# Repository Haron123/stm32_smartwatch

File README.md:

# stm32_smartwatch
a Project in which i Design a PCB for a STM32 based Smartwatch and eventually Programm it with FreeRTOS

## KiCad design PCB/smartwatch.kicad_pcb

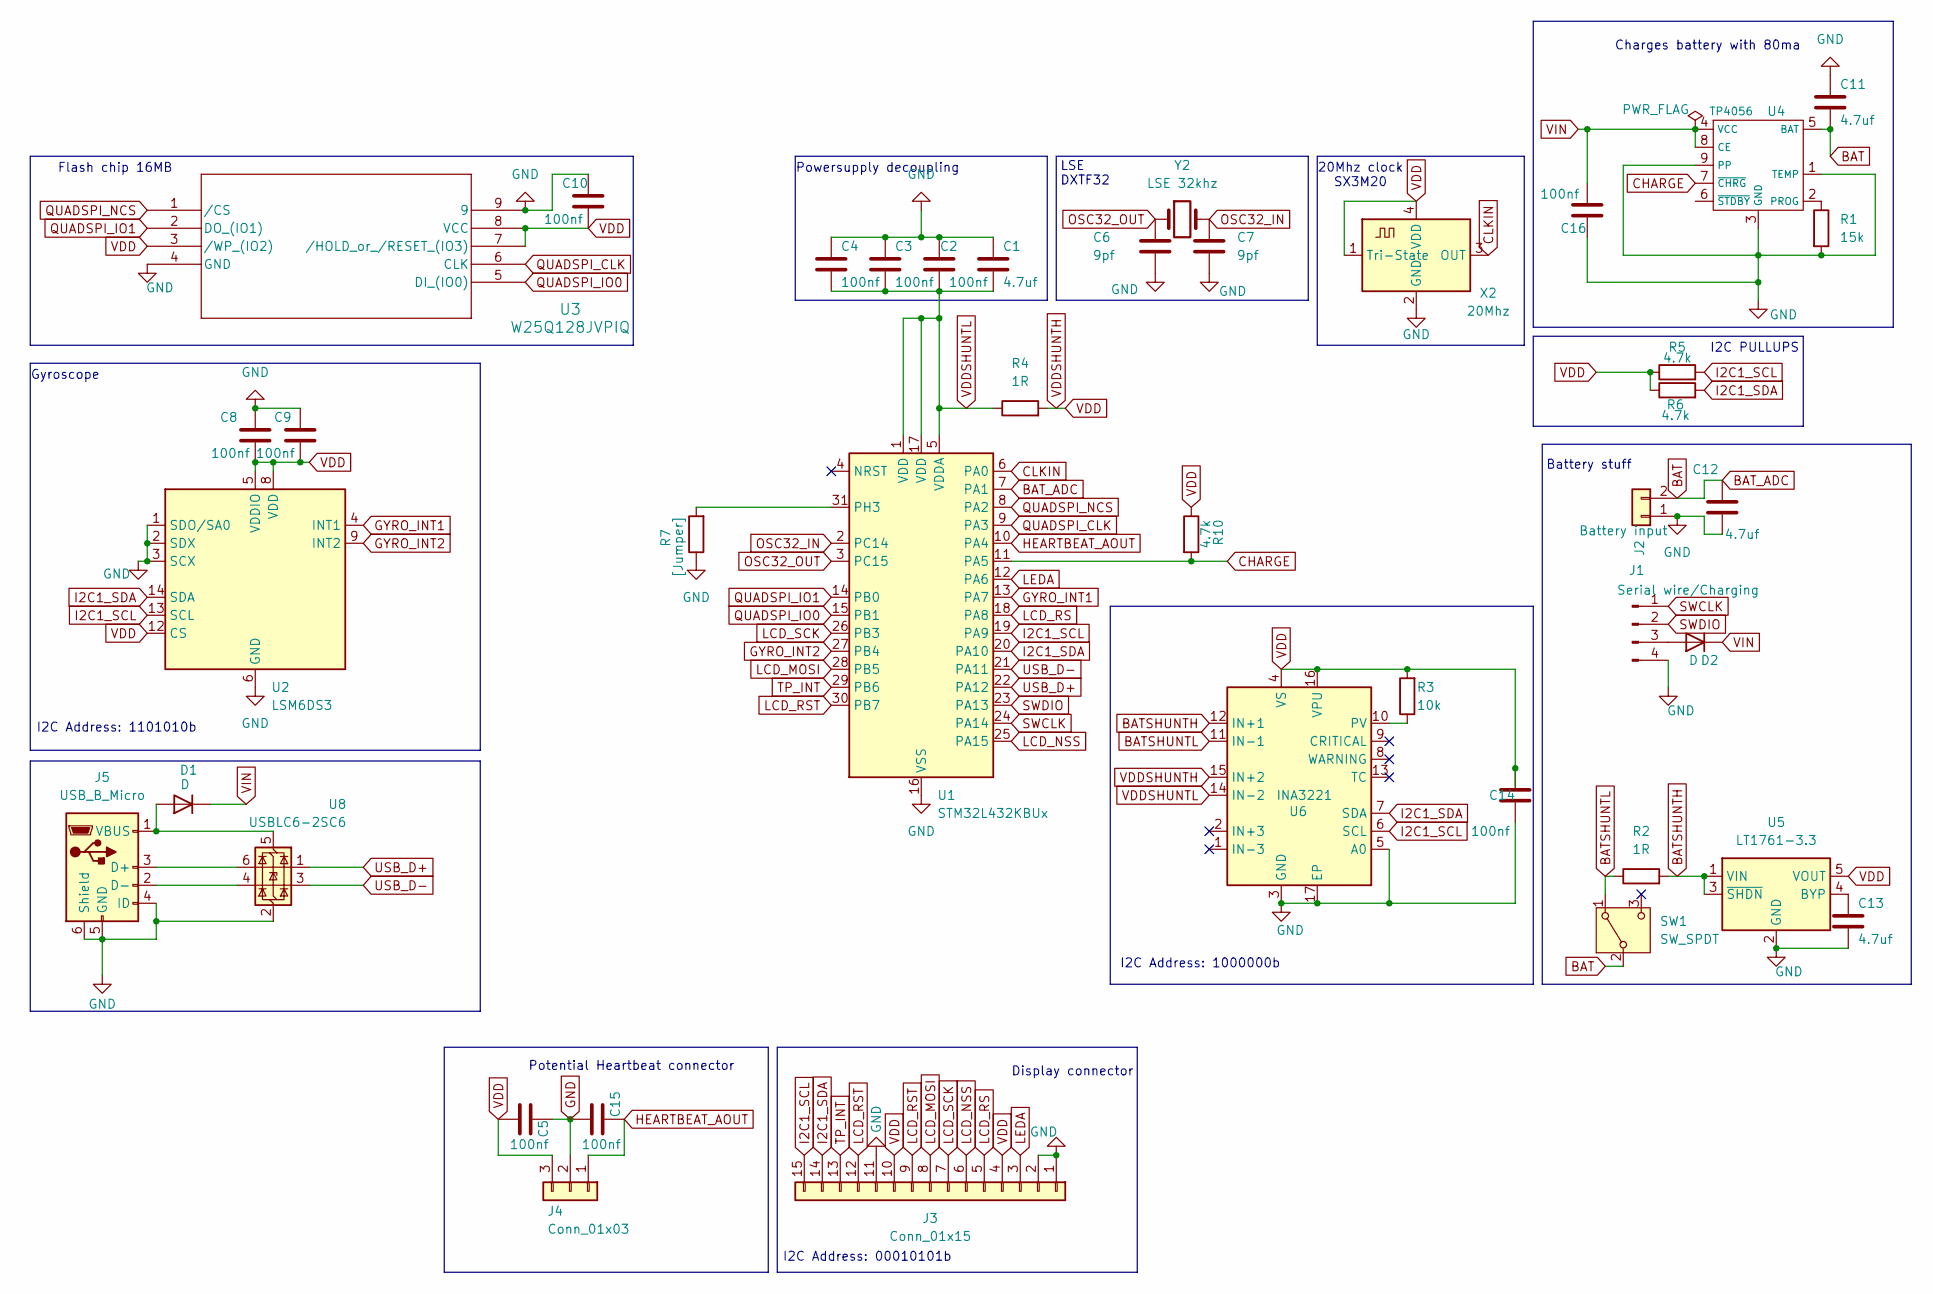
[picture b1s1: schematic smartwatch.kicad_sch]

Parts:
C1, C11, C12, C13: 4.7uf; C_0603_1608Metric
C2, C3, C4, C5, C8, C9, C10, C14, C15, C16: 100nf; C_0603_1608Metric
C6, C7: 9pf; C_0603_1608Metric
D1, D2: D; D_0603_1608Metric
J1: Serial wire/Charging; PinHeader_1x04_P2.54mm_Vertical
J2: Battery input; PinHeader_1x02_P2.54mm_Vertical
J3: Conn_01x15; FPC-SMD_15P-P0.50_KH-FG0.5-H2.0-15P-SMT
J4: Conn_01x03; PinHeader_1x03_P2.54mm_Vertical
J5: USB_B_Micro; USB_Micro-B_Amphenol_10118194_Horizontal
R1: 15k; R_0805_2012Metric
R2, R4: 1R; R_0805_2012Metric
R3: 10k; R_0805_2012Metric
R5, R6, R10: 4.7k; R_0805_2012Metric
R7: [Jumper]; R_0805_2012Metric
SW1: SW_SPDT; MSK12CO2
U1: STM32L432KBUx; QFN-32-1EP_5x5mm_P0.5mm_EP3.45x3.45mm
U2: LSM6DS3; LGA-14_3x2.5mm_P0.5mm_LayoutBorder3x4y
U3: W25Q128JVPIQ; WSON-8-1EP_6x5mm_P1.27mm_EP3.4x4.3mm
U4: TP4056; MSOP-8-1EP_3x3mm_P0.65mm_EP2.5x3mm_Mask1.73x2.36mm
U5: LT1761-3.3; TSOT-23-5
U6: INA3221; Texas_RGV0016A_VQFN-16-1EP_4x4mm_P0.65mm_EP2.1x2.1mm
U8: USBLC6-2SC6; SOT-23-6
X2: 20Mhz; Crystal_SMD_3225-4Pin_3.2x2.5mm
Y2: LSE 32khz; Crystal_SMD_3215-2Pin_3.2x1.5mm

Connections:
BAT: C11.2, C12.1, J2.2, SW1.2 (B), U1.7 (PA1), U4.5 (BAT)
BATSHUNTH: R2.2, U5.1 (VIN), U5.3 (~SHDN), U6.12 (IN+1)
BATSHUNTL: R2.1, SW1.1 (A), U6.11 (IN-1)
CHARGE: R10.2, U1.11 (PA5), U4.7 (~CHRG)
CLKIN: U1.6 (PA0), X2.3 (OUT)
GND: C1.1, C2.1, C3.1, C4.1, C5.1, C6.2, C7.2, C8.1, C9.1, C10.1, C11.1, C12.2, C13.2, C14.2, C15.2, C16.1, J1.4, J2.1, J3.1, J3.2, J3.11, J4.2, J5.4 (ID), J5.5 (GND), J5.6 (Shield), R1.2, R7.1, U1.16 (VSS), U1.32 (VSS), U1.33 (VSS), U2.1 (SDO/SA0), U2.2 (SDX), U2.3 (SCX), U2.6 (GND), U2.7 (GND), U3.4 (GND), U3.9, U4.1 (TEMP), U4.3 (GND), U4.9 (PP), U5.2 (GND), U6.3 (GND), U6.5 (A0), U6.17 (EP), U8.2 (GND), X2.2 (GND)
GYRO_INT1: U1.13 (PA7), U2.4 (INT1)
GYRO_INT2: U1.27 (PB4), U2.9 (INT2)
HEARTBEAT_AOUT: C15.1, J4.1, U1.10 (PA4)
I2C1_SCL: J3.15, R5.2, U1.19 (PA9), U2.13 (SCL), U6.6 (SCL)
I2C1_SDA: J3.14, R6.2, U1.20 (PA10), U2.14 (SDA), U6.7 (SDA)
LCD_MOSI: J3.8, U1.28 (PB5)
LCD_NSS: J3.6, U1.25 (PA15)
LCD_RS: J3.5, U1.18 (PA8)
LCD_RST: J3.9, J3.12, U1.30 (PB7)
LCD_SCK: J3.7, U1.26 (PB3)
LEDA: J3.3, U1.12 (PA6)
unnamed: D1.2 (A), J5.1 (VBUS), U8.5 (VBUS)
unnamed: D2.2 (A), J1.3
unnamed: J5.3 (D+), U8.6 (I/O1)
unnamed: J5.2 (D-), U8.4 (I/O2)
unnamed: R7.2, U1.31 (PH3)
unnamed: R1.1, U4.2 (PROG)
unnamed: C13.1, U5.4 (BYP)
unnamed: R3.1, U6.10 (PV)
OSC32_IN: C7.1, U1.2 (PC14), Y2.2
OSC32_OUT: C6.1, U1.3 (PC15), Y2.1
QUADSPI_CLK: U1.9 (PA3), U3.6 (CLK)
QUADSPI_IO0: U1.15 (PB1), U3.5 (DI_(IO0))
QUADSPI_IO1: U1.14 (PB0), U3.2 (DO_(IO1))
QUADSPI_NCS: U1.8 (PA2), U3.1 (/CS)
SWCLK: J1.1, U1.24 (PA14)
SWDIO: J1.2, U1.23 (PA13)
TP_INT: J3.13, U1.29 (PB6)
USB_D+: U1.22 (PA12), U8.1 (I/O1)
USB_D-: U1.21 (PA11), U8.3 (I/O2)
VDD: C5.2, C8.2, C9.2, C10.2, C14.1, J3.4, J3.10, J4.3, R3.2, R4.2, R5.1, R6.1, R10.1, U2.5 (VDDIO), U2.8 (VDD), U2.12 (CS), U3.3 (/WP_(IO2)), U3.7 (/HOLD_or_/RESET_(IO3)), U3.8 (VCC), U5.5 (VOUT), U6.4 (VS), U6.15 (IN+2), U6.16 (VPU), X2.1 (Tri-State), X2.4 (VDD)
VDDSHUNTL: C1.2, C2.2, C3.2, C4.2, R4.1, U1.1 (VDD), U1.5 (VDDA), U1.17 (VDD), U6.14 (IN-2)
VIN: C16.2, D1.1 (K), D2.1 (K), U4.4 (VCC), U4.8 (CE)

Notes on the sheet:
I2C Address: 1000000b
Potential Heartbeat connector
LSE DXTF32
Battery stuff
I2C Address: 1101010b
I2C PULLUPS
Flash chip 16MB
I2C Address: 00010101b
Charges battery with 80ma
20Mhz clock SX3M20
Powersupply decoupling
Gyroscope
Display connector

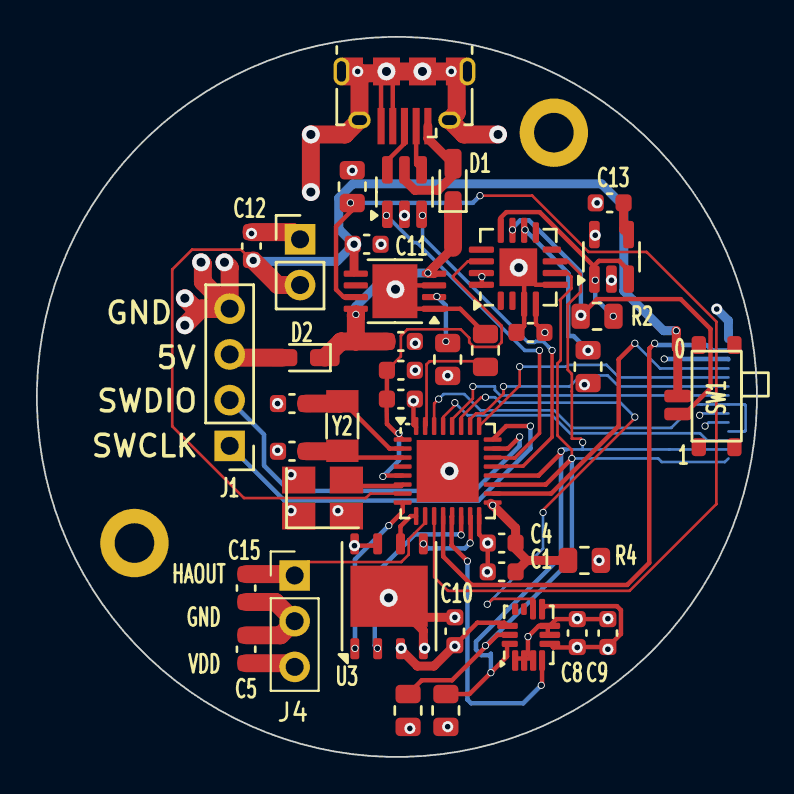
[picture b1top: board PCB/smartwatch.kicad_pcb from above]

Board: 4 copper layers, 40.0 x 40.0 mm, 41 parts (1 on the bottom side), 39 nets.

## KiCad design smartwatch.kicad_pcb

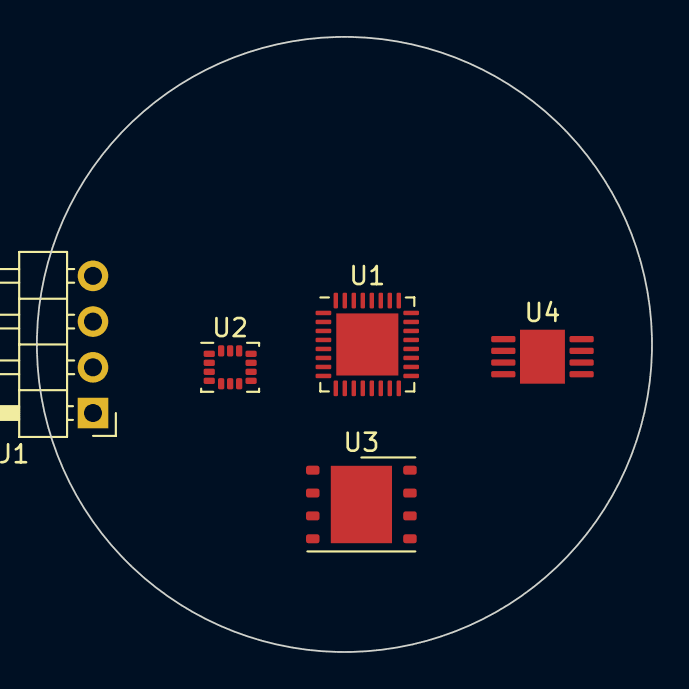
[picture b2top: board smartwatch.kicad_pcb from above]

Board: 2 copper layers, 34.2 x 34.2 mm, 5 parts (0 on the bottom side), 2 nets, no tracks yet.

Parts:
J1: Conn_01x04_Pin; PinHeader_1x04_P2.54mm_Horizontal
U1: STM32L432KBUx; QFN-32-1EP_5x5mm_P0.5mm_EP3.45x3.45mm
U2: LSM6DS3; LGA-14_3x2.5mm_P0.5mm_LayoutBorder3x4y
U3: W25Q128JVPIQ; WSON-8-1EP_6x5mm_P1.27mm_EP3.4x4.3mm
U4: TP4056; MSOP-8-1EP_3x3mm_P0.65mm_EP2.5x3mm_Mask1.73x2.36mm

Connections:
unnamed: U1.16 (VSS), U1.32 (VSS), U1.33 (VSS)
unnamed: U2.6 (GND), U2.7 (GND)

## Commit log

2024-05-16 PCB Design start
2024-05-16 folder for pcb
2024-05-16 deleted redundant files
2024-05-16 Added gyroscope
2024-06-26 new staffz
2024-06-26 files?
2024-06-27 tighter pcb
2024-07-29 All but routing done
2024-08-07 pcb done
